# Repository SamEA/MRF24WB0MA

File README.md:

MRF24WB0MA
==========

A breakout board for Microchip WiFi module MRF24WB0MA

Datasheet http://www.microchip.com/wwwproducts/Devices.aspx?dDocName=en548014

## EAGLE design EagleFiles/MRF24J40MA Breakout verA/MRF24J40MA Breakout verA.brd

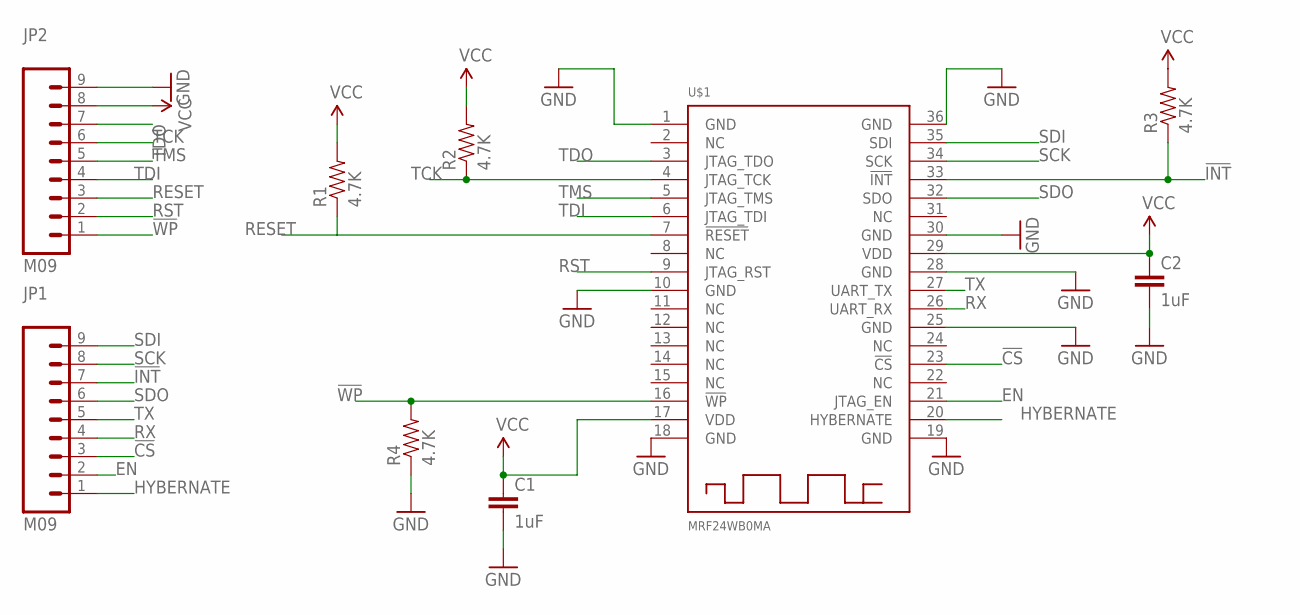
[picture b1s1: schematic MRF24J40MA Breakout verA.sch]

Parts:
C1, C2: 1uF; 0603-CAP
JP1, JP2: M09; 1X09
R1, R2, R3, R4: 4.7K; 0603-RES
U$1: MRF24WB0MA

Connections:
!CS: JP1.3, U$1.23 (!CS)
!INT: JP1.7, R3.1, U$1.33 (!INT)
!WP: JP2.1, R4.2, U$1.16 (!WP)
EN: JP1.2, U$1.21 (JTAG_EN)
GND: C1.2, C2.2, JP2.9, R4.1, U$1.1 (GND), U$1.10 (GND), U$1.18 (GND), U$1.19 (GND), U$1.25 (GND), U$1.28 (GND), U$1.30 (GND), U$1.36 (GND)
HYBERNATE: JP1.1, U$1.20 (HYBERNATE)
RESET: JP2.3, R1.1, U$1.7 (!RESET)
RST: JP2.2, U$1.9 (JTAG_RST)
RX: JP1.4, U$1.26 (UART_RX)
SCK: JP1.8, U$1.34 (SCK)
SDI: JP1.9, U$1.35 (SDI)
SDO: JP1.6, U$1.32 (SDO)
TCK: JP2.6, R2.1, U$1.4 (JTAG_TCK)
TDI: JP2.4, U$1.6 (JTAG_TDI)
TDO: JP2.7, U$1.3 (JTAG_TDO)
TMS: JP2.5, U$1.5 (JTAG_TMS)
TX: JP1.5, U$1.27 (UART_TX)
VCC: C1.1, C2.1, JP2.8, R1.2, R2.2, R3.2, U$1.17 (VDD), U$1.29 (VDD)

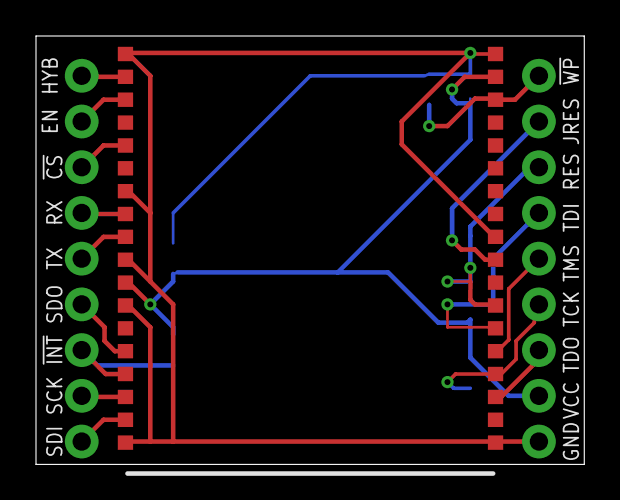
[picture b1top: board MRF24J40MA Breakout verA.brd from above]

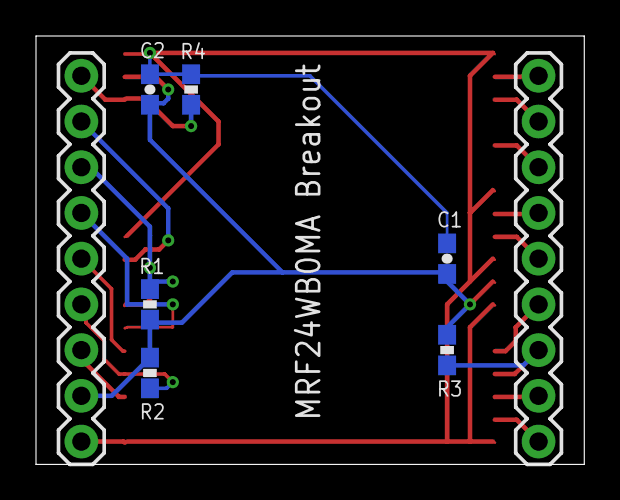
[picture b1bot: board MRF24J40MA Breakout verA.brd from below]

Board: 2 copper layers, 30.5 x 23.8 mm, 9 parts (8 on the bottom side), 18 nets.

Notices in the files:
parts and their libraries:
SparkFun-Passives: Licensing: CC v3.0 Share-Alike You are welcome to use this library for commercial purposes.
